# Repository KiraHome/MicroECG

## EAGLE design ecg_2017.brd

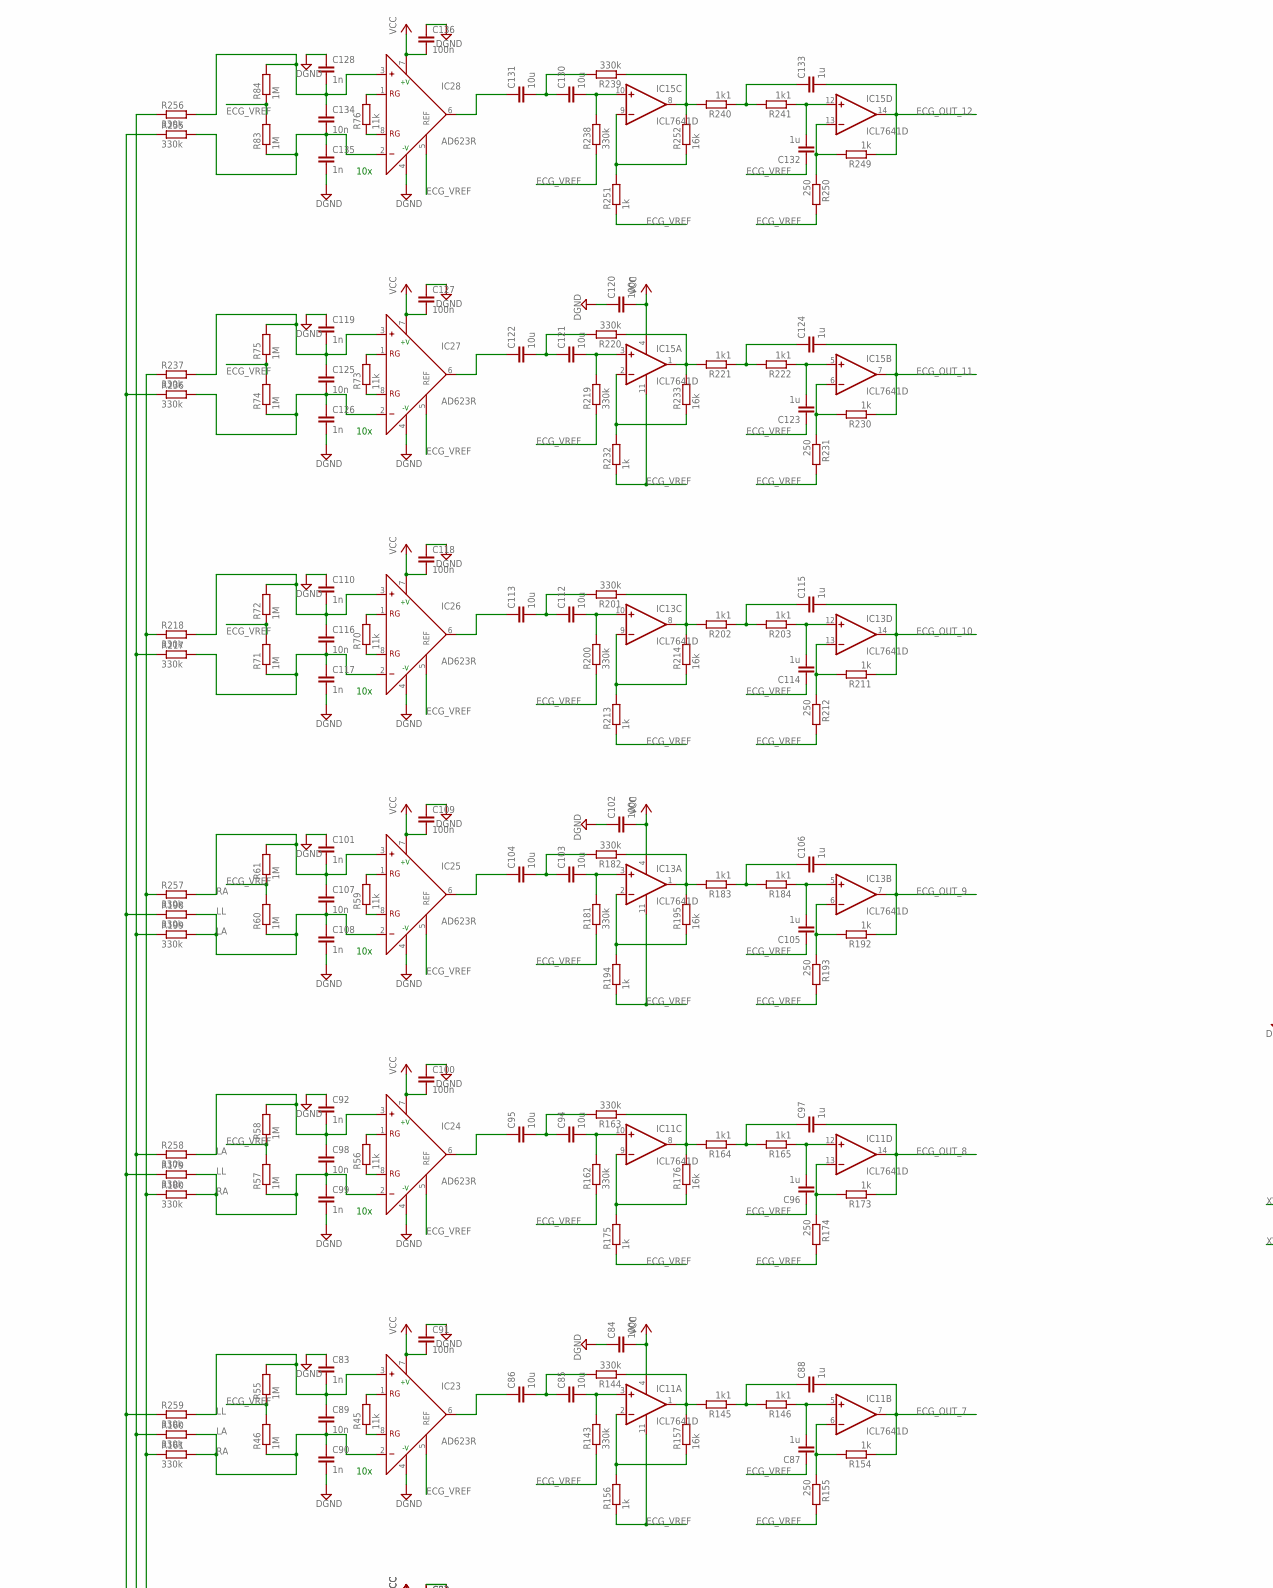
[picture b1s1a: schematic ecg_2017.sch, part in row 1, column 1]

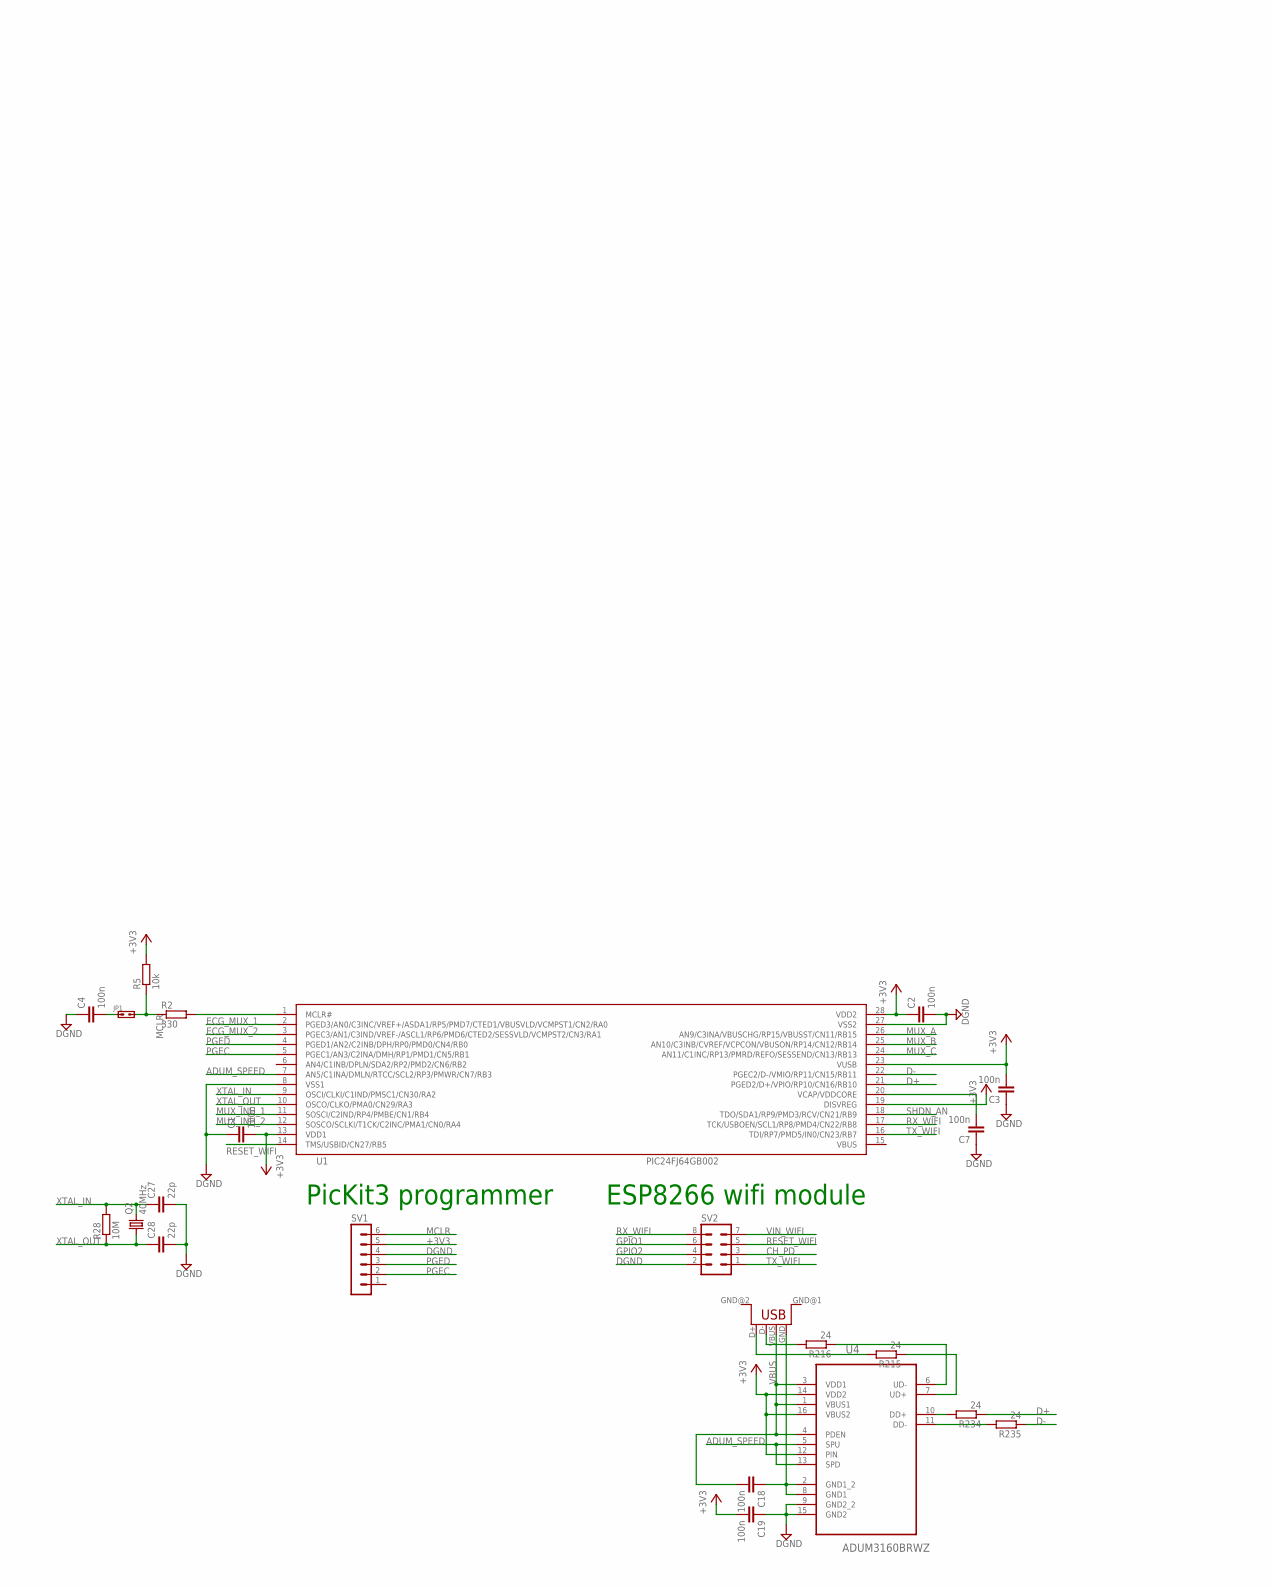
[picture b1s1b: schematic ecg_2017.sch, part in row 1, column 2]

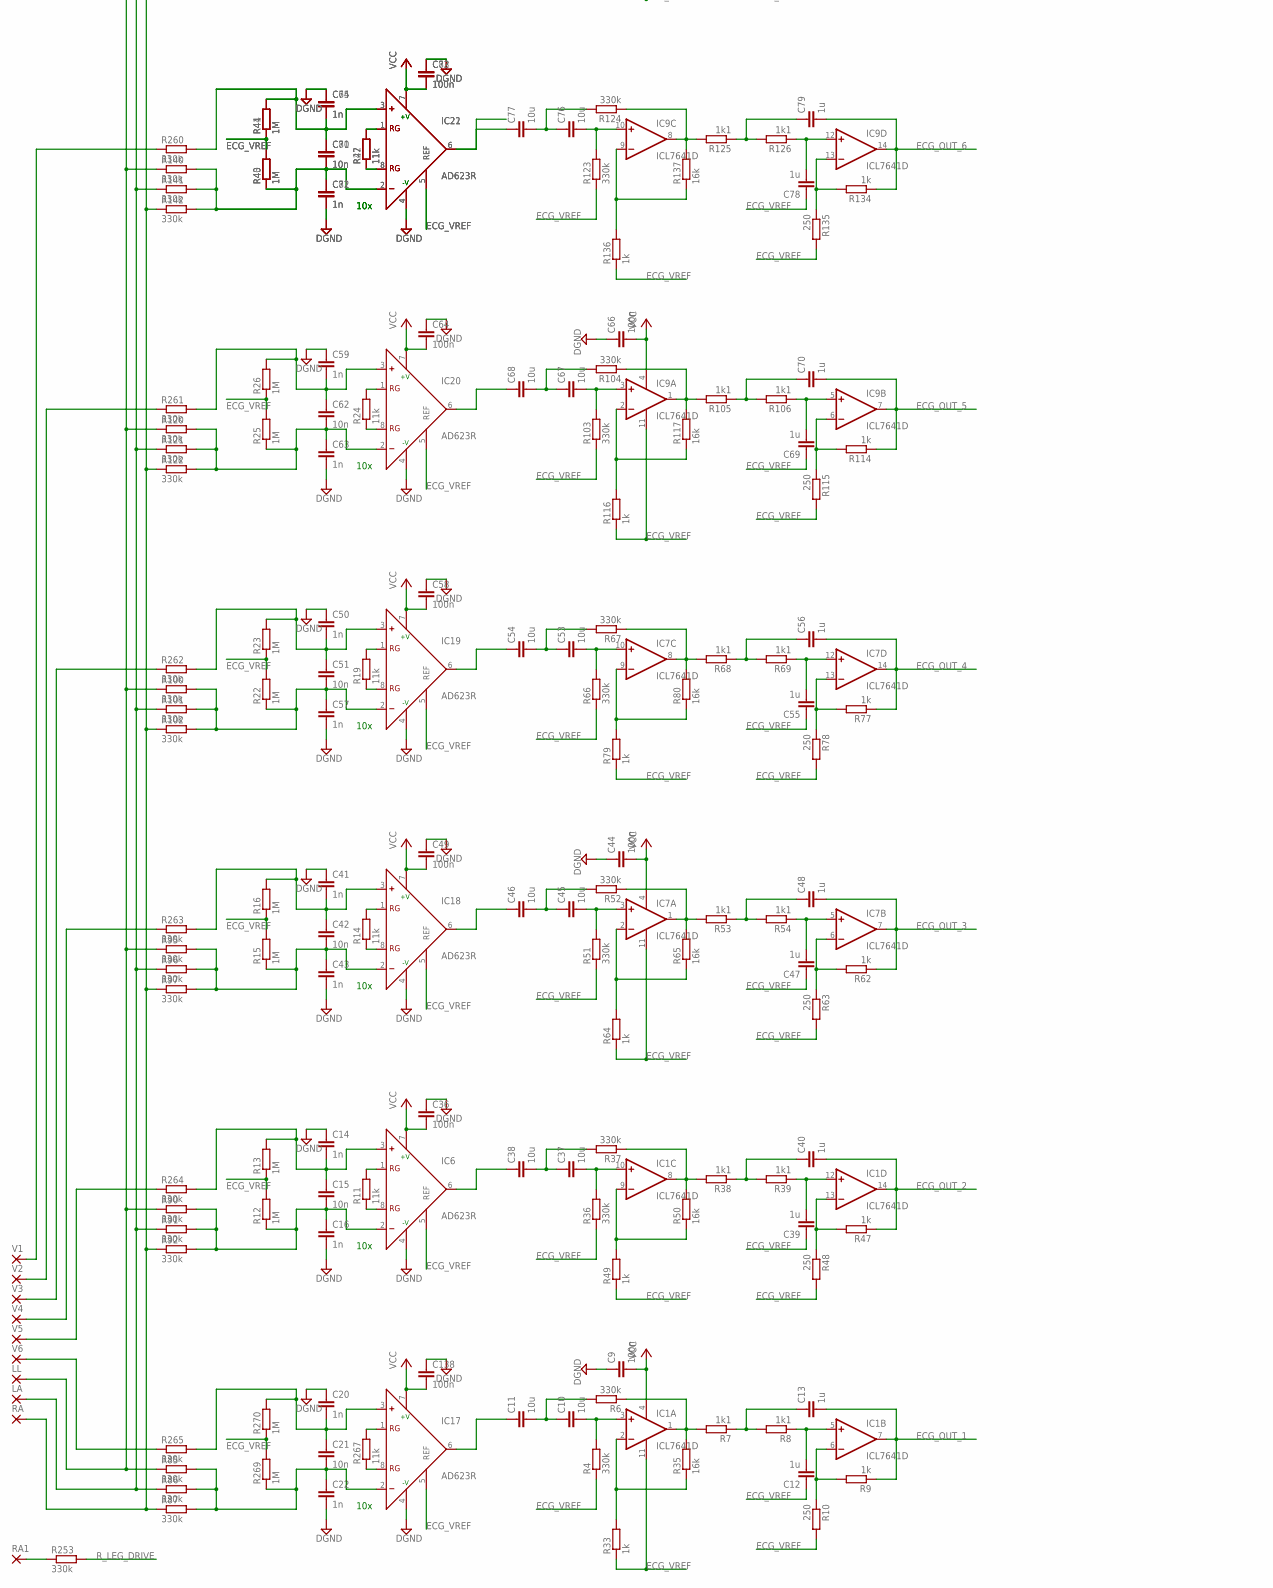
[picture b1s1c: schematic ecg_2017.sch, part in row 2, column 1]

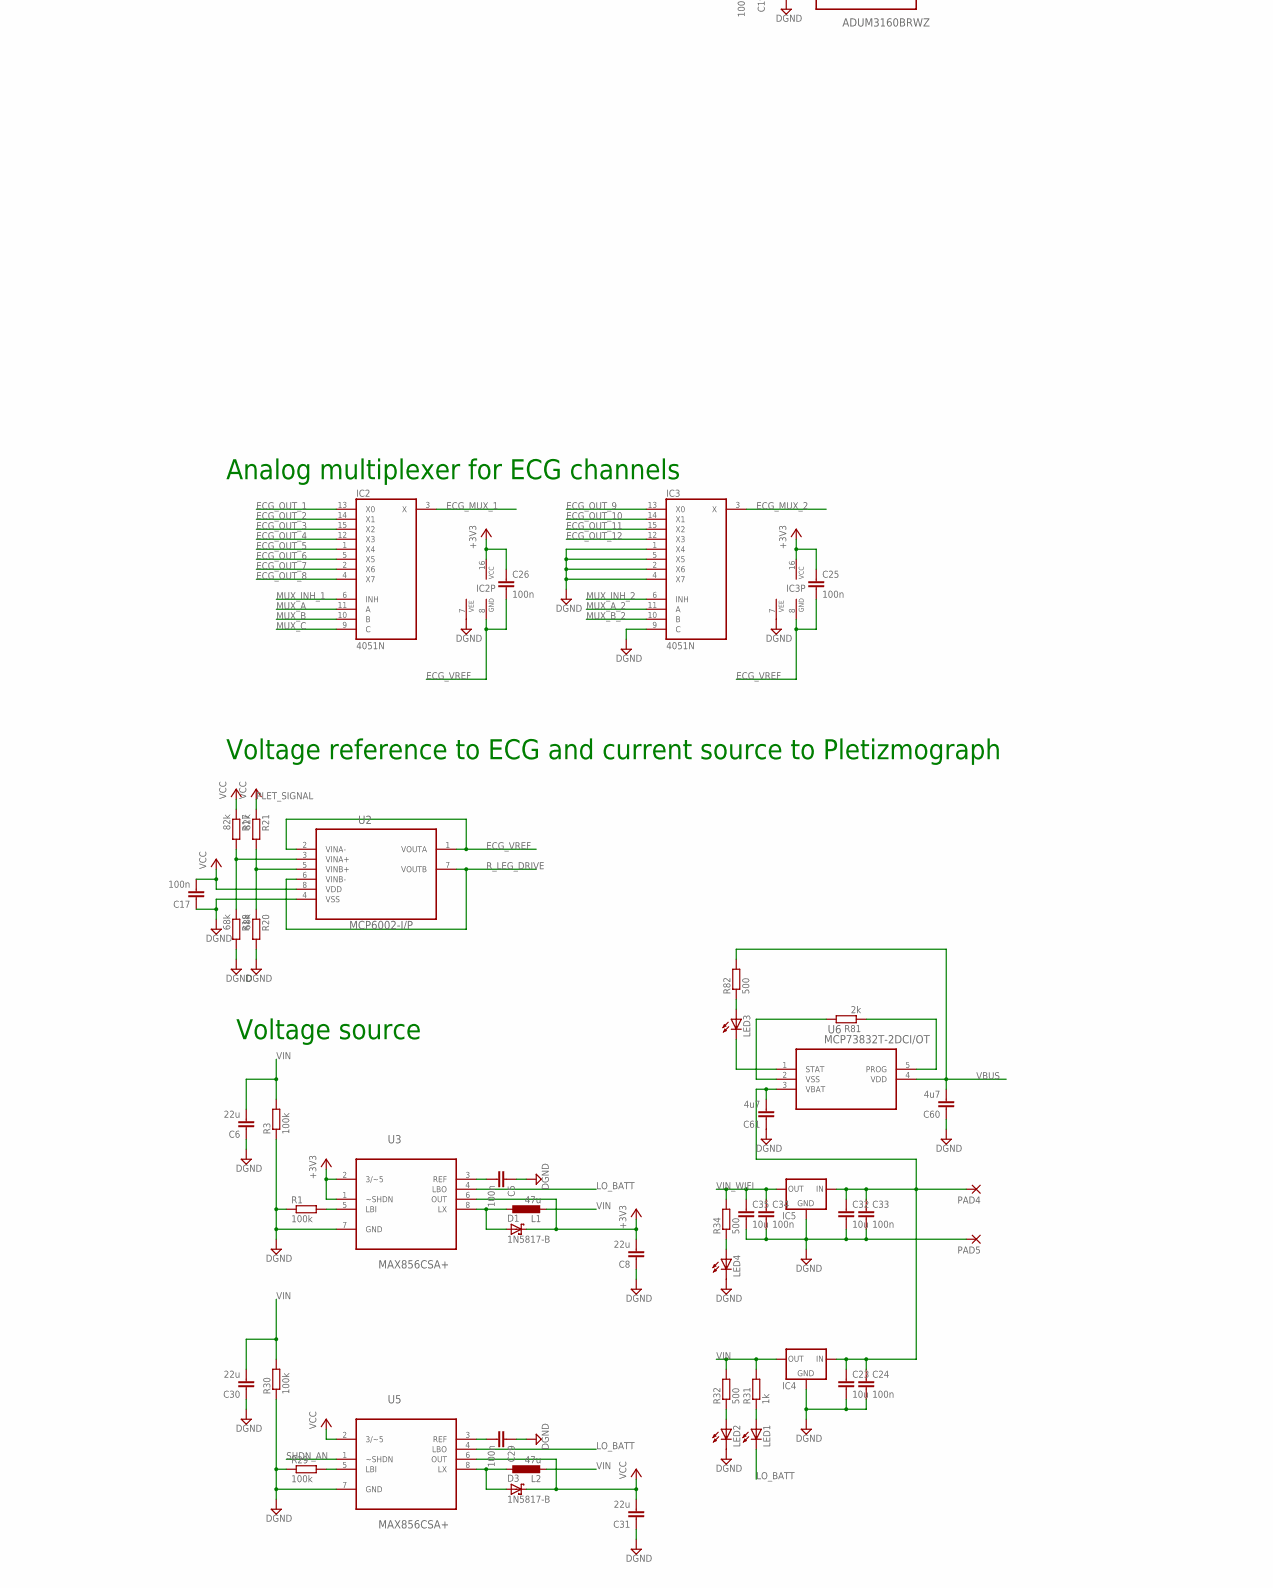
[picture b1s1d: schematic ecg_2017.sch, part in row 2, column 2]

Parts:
C1, C2, C3, C4, C5, C7, C9, C17, C18, C19, C24, C25, C26, C29, C33, C34, C36, C44, C49, C58, C64, C66, C73, C82, C84, C91, C100, C102, C109, C118, C120, C127, C136, C138: 100n; C0805
C6, C8, C30, C31: 22u; C0805
C10, C11, C23, C32, C35, C37, C38, C45, C46, C53, C54, C67, C68, C76, C77, C85, C86, C94, C95, C103, C104, C112, C113, C121, C122, C130, C131: 10u; C0805
C12, C13, C39, C40, C47, C48, C55, C56, C69, C70, C78, C79, C87, C88, C96, C97, C105, C106, C114, C115, C123, C124, C132, C133: 1u; C0805
C14, C16, C20, C22, C41, C43, C50, C57, C59, C63, C65, C72, C74, C81, C83, C90, C92, C99, C101, C108, C110, C117, C119, C126, C128, C135: 1n; C0805
C15, C21, C42, C51, C62, C71, C80, C89, C98, C107, C116, C125, C134: 10n; C0805
C27, C28: 22p; C0805
C60, C61: 4u7; C0805
CON2: USB; USB-FEMALE-A-PTH
D1, D3: 1N5817-B; DO41-7.6
IC1, IC7, IC9, IC11, IC13, IC15: ICL7641D; SO14
IC2, IC3: 4051N; DIL16
IC4, IC5: R-783.3-0.5; R-78XX
IC6, IC17, IC18, IC19, IC20, IC21, IC22, IC23, IC24, IC25, IC26, IC27, IC28: AD623R; SO8
JP1: JMP2; JP2
L1, L2: 47u; L1812
LA: 2,54/1,0
LED1, LED2, LED3, LED4: LEDSML0805; SML0805
LL: 2,54/1,0
PAD4, PAD5: 2,54/1,0
Q2: 40MHz; TC26V
R1, R3, R29, R30: 100k; R0805
R2: 330; R0805
R4, R6, R36, R37, R51, R52, R66, R67, R85, R86, R87, R90, R91, R92, R95, R96, R97, R100, R101, R102, R103, R104, R120, R121, R122, R123, R124, R140, R141, R142, R143, R144, R160, R161, R162, R163, R179, R180, R181, R182, R198, R199, R200, R201, R217, R218, R219, R220, R236, R237, R238, R239, R253, R255, R256, R257, R258, R259, R260, R261, R262, R263, R264, R265: 330k; R0805
R5: 10k; R0805
R7, R8, R38, R39, R53, R54, R68, R69, R105, R106, R125, R126, R145, R146, R164, R165, R183, R184, R202, R203, R221, R222, R240, R241: 1k1; R0805
R9, R31, R33, R47, R49, R62, R64, R77, R79, R114, R116, R134, R136, R154, R156, R173, R175, R192, R194, R211, R213, R230, R232, R249, R251: 1k; R0805
R10, R48, R63, R78, R115, R135, R155, R174, R193, R212, R231, R250: 250; R0805
R11, R14, R19, R24, R27, R42, R45, R56, R59, R70, R73, R76, R267: 11k; R0805
R12, R13, R15, R16, R22, R23, R25, R26, R40, R41, R43, R44, R46, R55, R57, R58, R60, R61, R71, R72, R74, R75, R83, R84, R269, R270: 1M; R0805
R17, R21: 82k; R0805
R18, R20: 68k; R0805
R28: 10M; M0805
R32, R34, R82: 500; R0805
R35, R50, R65, R80, R117, R137, R157, R176, R195, R214, R233, R252: 16k; R0805
R81: 2k; R0805
R215, R216, R234, R235: 24; R0805
RA, RA1: 2,54/1,0
SV1: MA06-1
SV2: MA04-2
U1: PIC24FJ64GB002; DIP28
U2: MCP6002-I/P; DIP254P762X533-8
U3, U5: MAX856CSA+; SOIC127P600X175-8N
U4: ADUM3160BRWZ; SOIC127P1032X265-16N
U6: MCP73832T-2DCI/OT; SOT95P300X145-5N
V1, V2, V3, V4, V5, V6: 2,54/1,0

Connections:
+3V3: C1.2, C2.1, C3.2, C8.2, C19.2, C25.1, C26.1, D1.C, IC2.16 (VCC), IC3.16 (VCC), R5.2, SV1.5, U1.13 (VDD1), U1.19 (DISVREG), U1.23 (VUSB), U1.28 (VDD2), U3.1 (~SHDN), U3.2 (3/~5), U3.6 (OUT), U4.12 (PIN), U4.14 (VDD2), U4.16 (VBUS2)
ADUM_SPEED: U1.7 (AN5/C1INA/DMLN/RTCC/SCL2/RP3/PMWR/CN7/R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), U4.5 (SPU), U4.13 (SPD)
CH_PD: SV2.3
D+: R234.1, U1.21 (PGED2/D+/VPIO/RP10/CN16/RB10)
D-: R235.1, U1.22 (PGEC2/D-/VMIO/RP11/CN15/RB11)
DGND: C1.1, C2.2, C3.1, C4.1, C5.1, C6.1, C7.1, C8.1, C9.1, C14.2, C16.1, C17.1, C19.1, C20.2, C22.1, C23.2, C24.2, C27.2, C28.2, C29.1, C30.1, C31.1, C32.2, C33.2, C34.2, C35.2, C36.2, C41.2, C43.1, C44.1, C49.2, C50.2, C57.1, C58.2, C59.2, C60.1, C61.1, C63.1, C64.2, C65.2, C66.1, C72.1, C73.2, C74.2, C81.1, C82.2, C83.2, C84.1, C90.1, C91.2, C92.2, C99.1, C100.2, C101.2, C102.1, C108.1, C109.2, C110.2, C117.1, C118.2, C119.2, C120.1, C126.1, C127.2, C128.2, C135.1, C136.2, C138.2, IC2.7 (VEE), IC3.1 (X4), IC3.2 (X6), IC3.4 (X7), IC3.5 (X5), IC3.7 (VEE), IC3.9 (C), IC4.GND, IC5.GND, IC6.4 (-V), IC17.4 (-V), IC18.4 (-V), IC19.4 (-V), IC20.4 (-V), IC21.4 (-V), IC22.4 (-V), IC23.4 (-V), IC24.4 (-V), IC25.4 (-V), IC26.4 (-V), IC27.4 (-V), IC28.4 (-V), LED2.C, LED4.C, PAD5.1, R1.1, R3.1, R18.2, R20.2, R29.1, R30.1, SV1.4, SV2.2, U1.8 (VSS1), U1.27 (VSS2), U2.4 (VSS), U3.7 (GND), U4.9 (GND2_2), U4.15 (GND2), U5.7 (GND)
ECG_MUX_1: IC2.3 (X), U1.2 (PGED3/AN0/C3INC/VREF+/ASDA1/RP5/PMD7/CT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)
ECG_MUX_2: IC3.3 (X), U1.3 (PGEC3/AN1/C3IND/VREF-/ASCL1/RP6/PMD6/CT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)
ECG_OUT_1: C13.2, IC1.7 (OUT), IC2.13 (X0), R9.1
ECG_OUT_2: C40.2, IC1.14 (OUT), IC2.14 (X1), R47.1
ECG_OUT_3: C48.2, IC2.15 (X2), IC7.7 (OUT), R62.1
ECG_OUT_4: C56.2, IC2.12 (X3), IC7.14 (OUT), R77.1
ECG_OUT_5: C70.2, IC2.1 (X4), IC9.7 (OUT), R114.1
ECG_OUT_6: C79.2, IC2.5 (X5), IC9.14 (OUT), R134.1
ECG_OUT_7: C88.2, IC2.2 (X6), IC11.7 (OUT), R154.1
ECG_OUT_8: C97.2, IC2.4 (X7), IC11.14 (OUT), R173.1
ECG_OUT_9: C106.2, IC3.13 (X0), IC13.7 (OUT), R192.1
ECG_OUT_10: C115.2, IC3.14 (X1), IC13.14 (OUT), R211.1
ECG_OUT_11: C124.2, IC3.15 (X2), IC15.7 (OUT), R230.1
ECG_OUT_12: C133.2, IC3.12 (X3), IC15.14 (OUT), R249.1
ECG_VREF: C12.1, C25.2, C26.2, C39.1, C47.1, C55.1, C69.1, C78.1, C87.1, C96.1, C105.1, C114.1, C123.1, C132.1, IC1.11 (V-), IC2.8 (GND), IC3.8 (GND), IC6.5 (REF), IC7.11 (V-), IC9.11 (V-), IC11.11 (V-), IC13.11 (V-), IC15.11 (V-), IC17.5 (REF), IC18.5 (REF), IC19.5 (REF), IC20.5 (REF), IC21.5 (REF), IC22.5 (REF), IC23.5 (REF), IC24.5 (REF), IC25.5 (REF), IC26.5 (REF), IC27.5 (REF), IC28.5 (REF), R4.1, R10.2, R12.2, R13.1, R15.2, R16.1, R22.2, R23.1, R25.2, R26.1, R33.1, R36.1, R40.2, R41.1, R43.2, R44.1, R46.2, R48.2, R49.1, R51.1, R55.1, R57.2, R58.1, R60.2, R61.1, R63.2, R64.1, R66.1, R71.2, R72.1, R74.2, R75.1, R78.2, R79.1, R83.2, R84.1, R103.1, R115.2, R116.1, R123.1, R135.2, R136.1, R143.1, R155.2, R156.1, R162.1, R174.2, R175.1, R181.1, R193.2, R194.1, R200.1, R212.2, R213.1, R219.1, R231.2, R232.1, R238.1, R250.2, R251.1, R269.2, R270.1, U2.1 (VOUTA), U2.2 (VINA-)
GPIO1: SV2.6
GPIO2: SV2.4
LA: LA.1, R86.1, R91.1, R96.1, R101.1, R121.1, R141.1, R160.1, R199.1, R217.1, R256.1, R258.1
LL: LL.1, R85.1, R90.1, R95.1, R100.1, R120.1, R140.1, R179.1, R198.1, R236.1, R255.1, R259.1
LO_BATT: LED1.C, U3.4 (LBO), U5.4 (LBO)
MCLR: JP1.2, R2.1, R5.1, SV1.6
MUX_A: IC2.11 (A), U1.26 (AN9/C3INA/VBUSCHG/RP15/VBUSST/CN11/RB15)
MUX_A_2: IC3.11 (A)
MUX_B: IC2.10 (B), U1.25 (AN10/C3INB/CVREF/VCPCON/VBUSON/RP14/CN1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)
MUX_B_2: IC3.10 (B)
MUX_C: IC2.9 (C), U1.24 (AN11/C1INC/RP13/PMRD/REFO/SESSEND/CN13/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)
MUX_INH_1: IC2.6 (INH), U1.11 (SOSCI/C2IND/RP4/PMBE/CN1/RB4)
MUX_INH_2: IC3.6 (INH), U1.12 (SOSCO/SCLKI/T1CK/C2INC/PMA1/CN0/RA4)
unnamed: C5.2, U3.3 (REF)
unnamed: R1.2, U3.5 (LBI)
unnamed: C10.2, IC1.3 (+IN), R4.2
unnamed: D1.A, L1.1, U3.8 (LX)
unnamed: C10.1, C11.2, R6.2
unnamed: IC1.2 (-IN), R33.2, R35.1
unnamed: C13.1, R7.1, R8.2
unnamed: C12.2, IC1.5 (+IN), R8.1
unnamed: IC6.8 (RG), R11.1
unnamed: C4.2, JP1.1
unnamed: R2.2, U1.1 (MCLR#)
unnamed: IC6.1 (RG), R11.2
unnamed: C134.1, C135.2, IC28.2 (-), R83.1, R255.2
unnamed: C14.1, C15.2, IC6.3 (+), R13.2, R264.2
unnamed: C38.1, IC6.6 (OUT)
unnamed: IC18.8 (RG), R14.1
unnamed: IC18.1 (RG), R14.2
unnamed: R17.2, R18.1, U2.3 (VINA+)
unnamed: IC17.8 (RG), R267.1
unnamed: IC1.6 (-IN), R9.2, R10.1
unnamed: C41.1, C42.2, IC18.3 (+), R16.2, R263.2
unnamed: C29.2, U5.3 (REF)
unnamed: C46.1, IC18.6 (OUT)
unnamed: IC19.8 (RG), R19.1
unnamed: C23.1, C24.1, C32.1, C33.1, C61.2, IC4.IN, IC5.IN, PAD4.1, U6.3 (VBAT)
unnamed: R81.1, U6.5 (PROG)
unnamed: R81.2, U6.2 (VSS)
unnamed: LED3.A, R82.1
unnamed: LED3.C, U6.1 (STAT)
unnamed: IC19.1 (RG), R19.2
unnamed: C50.1, C51.2, IC19.3 (+), R23.2, R262.2
unnamed: C54.1, IC19.6 (OUT)
unnamed: IC28.8 (RG), R76.1
unnamed: IC20.8 (RG), R24.1
unnamed: IC20.1 (RG), R24.2
unnamed: C59.1, C62.2, IC20.3 (+), R26.2, R261.2
unnamed: C68.1, IC20.6 (OUT)
unnamed: R29.2, U5.5 (LBI)
unnamed: C7.2, U1.20 (VCAP/VDDCORE)
unnamed: D3.A, L2.1, U5.8 (LX)
unnamed: LED1.A, R31.1
unnamed: LED2.A, R32.1
unnamed: C37.2, IC1.10 (+IN), R36.2
unnamed: IC1.1 (OUT), R6.1, R7.2, R35.2
unnamed: LED4.A, R34.1
unnamed: C37.1, C38.2, R37.2
unnamed: C40.1, R38.1, R39.2
unnamed: C39.2, IC1.12 (+IN), R39.1
unnamed: IC28.1 (RG), R76.2
unnamed: IC21.8 (RG), R27.1
unnamed: IC21.1 (RG), R27.2
unnamed: C65.1, C71.2, IC21.3 (+), R41.2, R260.2
unnamed: C77.1, IC21.6 (OUT)
unnamed: IC17.1 (RG), R267.2
unnamed: C80.1, C81.2, IC22.2 (-), R43.1
unnamed: C89.1, C90.2, IC23.2 (-), R46.1, R160.2, R161.2
unnamed: IC1.13 (-IN), R47.2, R48.1
unnamed: IC1.8 (OUT), R37.1, R38.2, R50.2
unnamed: IC1.9 (-IN), R49.2, R50.1
unnamed: C45.2, IC7.3 (+IN), R51.2
unnamed: C45.1, C46.2, R52.2
unnamed: C48.1, R53.1, R54.2
unnamed: C47.2, IC7.5 (+IN), R54.1
unnamed: C98.1, C99.2, IC24.2 (-), R57.1, R179.2, R180.2
unnamed: C107.1, C108.2, IC25.2 (-), R60.1, R198.2, R199.2
unnamed: C116.1, C117.2, IC26.2 (-), R71.1, R217.2
unnamed: C125.1, C126.2, IC27.2 (-), R74.1, R236.2
unnamed: IC22.8 (RG), R42.1
unnamed: IC22.1 (RG), R42.2
unnamed: C74.1, C80.2, IC22.3 (+), R44.2
unnamed: IC7.6 (-IN), R62.2, R63.1
unnamed: IC7.1 (OUT), R52.1, R53.2, R65.2
unnamed: IC7.2 (-IN), R64.2, R65.1
unnamed: C53.2, IC7.10 (+IN), R66.2
unnamed: C53.1, C54.2, R67.2
unnamed: C56.1, R68.1, R69.2
unnamed: C55.2, IC7.12 (+IN), R69.1
unnamed: IC23.8 (RG), R45.1
unnamed: IC23.1 (RG), R45.2
unnamed: C83.1, C89.2, IC23.3 (+), R55.2, R259.2
unnamed: C86.1, IC23.6 (OUT)
unnamed: C20.1, C21.2, IC17.3 (+), R265.2, R270.2
unnamed: IC24.8 (RG), R56.1
unnamed: IC24.1 (RG), R56.2
unnamed: IC7.13 (-IN), R77.2, R78.1
unnamed: IC7.8 (OUT), R67.1, R68.2, R80.2
unnamed: IC7.9 (-IN), R79.2, R80.1
unnamed: C21.1, C22.2, IC17.2 (-), R85.2, R86.2, R87.2, R269.1
unnamed: C128.1, C134.2, IC28.3 (+), R84.2, R256.2
unnamed: C112.2, IC13.10 (+IN), R200.2
unnamed: C112.1, C113.2, R201.2
unnamed: R265.1, V6.1
unnamed: C92.1, C98.2, IC24.3 (+), R58.2, R258.2
unnamed: C15.1, C16.2, IC6.2 (-), R12.1, R90.2, R91.2, R92.2
unnamed: R264.1, V5.1
unnamed: C18.1, CON2.GND, U4.2 (GND1_2), U4.8 (GND1)
unnamed: C95.1, IC24.6 (OUT)
unnamed: C76.2, IC9.10 (+IN), R123.2
unnamed: R263.1, V4.1
unnamed: R216.1, U4.6 (UD-)
unnamed: R215.1, U4.7 (UD+)
unnamed: R262.1, V3.1
unnamed: C42.1, C43.2, IC18.2 (-), R15.1, R95.2, R96.2, R97.2
unnamed: C51.1, C57.2, IC19.2 (-), R22.1, R100.2, R101.2, R102.2
unnamed: C76.1, C77.2, R124.2
unnamed: C67.2, IC9.3 (+IN), R103.2
unnamed: C67.1, C68.2, R104.2
unnamed: C70.1, R105.1, R106.2
unnamed: C69.2, IC9.5 (+IN), R106.1
unnamed: IC25.8 (RG), R59.1
unnamed: IC25.1 (RG), R59.2
unnamed: C101.1, C107.2, IC25.3 (+), R61.2, R257.2
unnamed: C104.1, IC25.6 (OUT)
unnamed: C11.1, IC17.6 (OUT)
unnamed: IC26.8 (RG), R70.1
unnamed: IC26.1 (RG), R70.2
unnamed: IC9.6 (-IN), R114.2, R115.1
unnamed: IC9.1 (OUT), R104.1, R105.2, R117.2
unnamed: IC9.2 (-IN), R116.2, R117.1
unnamed: CON2.D-, R216.2
unnamed: R234.2, U4.10 (DD+)
unnamed: C110.1, C116.2, IC26.3 (+), R72.2, R218.2
unnamed: C62.1, C63.2, IC20.2 (-), R25.1, R120.2, R121.2, R122.2
unnamed: C79.1, R125.1, R126.2
unnamed: C78.2, IC9.12 (+IN), R126.1
unnamed: C113.1, IC26.6 (OUT)
unnamed: IC27.8 (RG), R73.1
unnamed: IC27.1 (RG), R73.2
unnamed: C119.1, C125.2, IC27.3 (+), R75.2, R237.2
unnamed: C122.1, IC27.6 (OUT)
unnamed: C131.1, IC28.6 (OUT)
unnamed: IC9.13 (-IN), R134.2, R135.1
unnamed: IC9.8 (OUT), R124.1, R125.2, R137.2
unnamed: IC9.9 (-IN), R136.2, R137.1
unnamed: CON2.D+, R215.2
unnamed: R235.2, U4.11 (DD-)
unnamed: R260.1, V1.1
unnamed: C71.1, C72.2, IC21.2 (-), R40.1, R140.2, R141.2, R142.2
unnamed: R261.1, V2.1
unnamed: C94.2, IC11.10 (+IN), R162.2
unnamed: C85.2, IC11.3 (+IN), R143.2
unnamed: C85.1, C86.2, R144.2
unnamed: C88.1, R145.1, R146.2
unnamed: C87.2, IC11.5 (+IN), R146.1
unnamed: IC11.6 (-IN), R154.2, R155.1
unnamed: IC11.1 (OUT), R144.1, R145.2, R157.2
unnamed: IC11.2 (-IN), R156.2, R157.1
unnamed: R253.1, RA1.1
unnamed: C94.1, C95.2, R163.2
unnamed: C115.1, R202.1, R203.2
unnamed: C97.1, R164.1, R165.2
unnamed: C96.2, IC11.12 (+IN), R165.1
unnamed: IC11.13 (-IN), R173.2, R174.1
unnamed: IC11.8 (OUT), R163.1, R164.2, R176.2
unnamed: IC11.9 (-IN), R175.2, R176.1
unnamed: C103.2, IC13.3 (+IN), R181.2
unnamed: C103.1, C104.2, R182.2
unnamed: C106.1, R183.1, R184.2
unnamed: C105.2, IC13.5 (+IN), R184.1
unnamed: IC13.6 (-IN), R192.2, R193.1
unnamed: IC13.1 (OUT), R182.1, R183.2, R195.2
unnamed: IC13.2 (-IN), R194.2, R195.1
unnamed: C114.2, IC13.12 (+IN), R203.1
unnamed: IC13.13 (-IN), R211.2, R212.1
unnamed: IC13.8 (OUT), R201.1, R202.2, R214.2
unnamed: IC13.9 (-IN), R213.2, R214.1
unnamed: C121.2, IC15.3 (+IN), R219.2
unnamed: C121.1, C122.2, R220.2
unnamed: C124.1, R221.1, R222.2
unnamed: C123.2, IC15.5 (+IN), R222.1
unnamed: IC15.6 (-IN), R230.2, R231.1
unnamed: IC15.1 (OUT), R220.1, R221.2, R233.2
unnamed: IC15.2 (-IN), R232.2, R233.1
unnamed: C130.2, IC15.10 (+IN), R238.2
unnamed: C130.1, C131.2, R239.2
unnamed: C133.1, R240.1, R241.2
unnamed: C132.2, IC15.12 (+IN), R241.1
unnamed: IC15.13 (-IN), R249.2, R250.1
unnamed: IC15.8 (OUT), R239.1, R240.2, R252.2
unnamed: IC15.9 (-IN), R251.2, R252.1
PGEC: SV1.2, U1.5 (PGEC1/AN3/C2INA/DMH/RP1/PMD1/CN5/RB1)
PGED: SV1.3, U1.4 (PGED1/AN2/C2INB/DPH/RP0/PMD0/CN4/RB0)
PLET_SIGNAL: R20.1, R21.2, U2.5 (VINB+)
RA: R87.1, R92.1, R97.1, R102.1, R122.1, R142.1, R161.1, R180.1, R218.1, R237.1, R257.1, RA.1
RESET_WIFI: SV2.5, U1.14 (TMS/USBID/CN27/RB5)
RX_WIFI: SV2.8, U1.17 (TCK/USBOEN/SCL1/RP8/PMD4/CN22/RB8)
R_LEG_DRIVE: R253.2, U2.6 (VINB-), U2.7 (VOUTB)
SHDN_AN: U1.18 (TDO/SDA1/RP9/PMD3/RCV/CN21/RB9), U5.1 (~SHDN)
TX_WIFI: SV2.1, U1.16 (TDI/RP7/PMD5/IN0/CN23/RB7)
VBUS: C18.2, C60.2, CON2.VBUS, R82.2, U1.15 (VBUS), U4.1 (VBUS1), U4.3 (VDD1), U4.4 (PDEN), U6.4 (VDD)
VCC: C9.2, C17.2, C31.2, C36.1, C44.2, C49.1, C58.1, C64.1, C66.2, C73.1, C82.1, C84.2, C91.1, C100.1, C102.2, C109.1, C118.1, C120.2, C127.1, C136.1, C138.1, D3.C, IC1.4 (V+), IC6.7 (+V), IC7.4 (V+), IC9.4 (V+), IC11.4 (V+), IC13.4 (V+), IC15.4 (V+), IC17.7 (+V), IC18.7 (+V), IC19.7 (+V), IC20.7 (+V), IC21.7 (+V), IC22.7 (+V), IC23.7 (+V), IC24.7 (+V), IC25.7 (+V), IC26.7 (+V), IC27.7 (+V), IC28.7 (+V), R17.1, R21.1, U2.8 (VDD), U5.2 (3/~5), U5.6 (OUT)
VIN: C6.2, C30.2, IC4.OUT, L1.2, L2.2, R3.2, R30.2, R31.2, R32.2
VIN_WIFI: C34.1, C35.1, IC5.OUT, R34.2, SV2.7
XTAL_IN: C27.1, Q2.2, R28.2, U1.9 (OSCI/CLKI/C1IND/PMSC1/CN30/RA2)
XTAL_OUT: C28.1, Q2.1, R28.1, U1.10 (OSCO/CLKO/PMA0/CN29/RA3)

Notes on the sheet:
PicKit3 programmer
ESP8266 wifi module
Voltage source
Voltage reference to ECG and current source to Pletizmograph
Analog multiplexer for ECG channels
10x

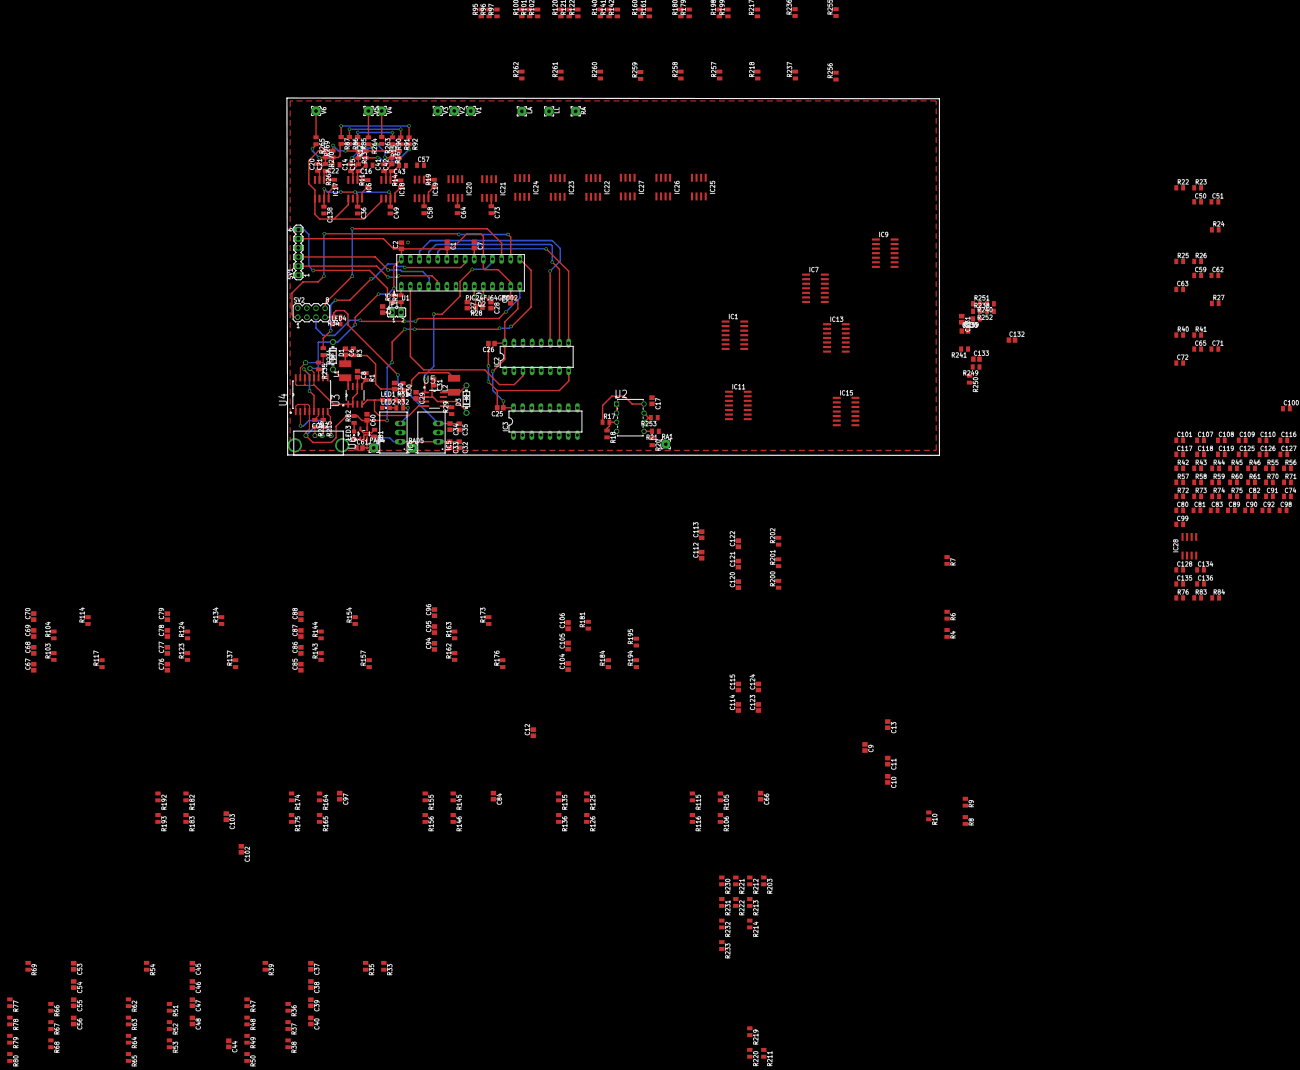
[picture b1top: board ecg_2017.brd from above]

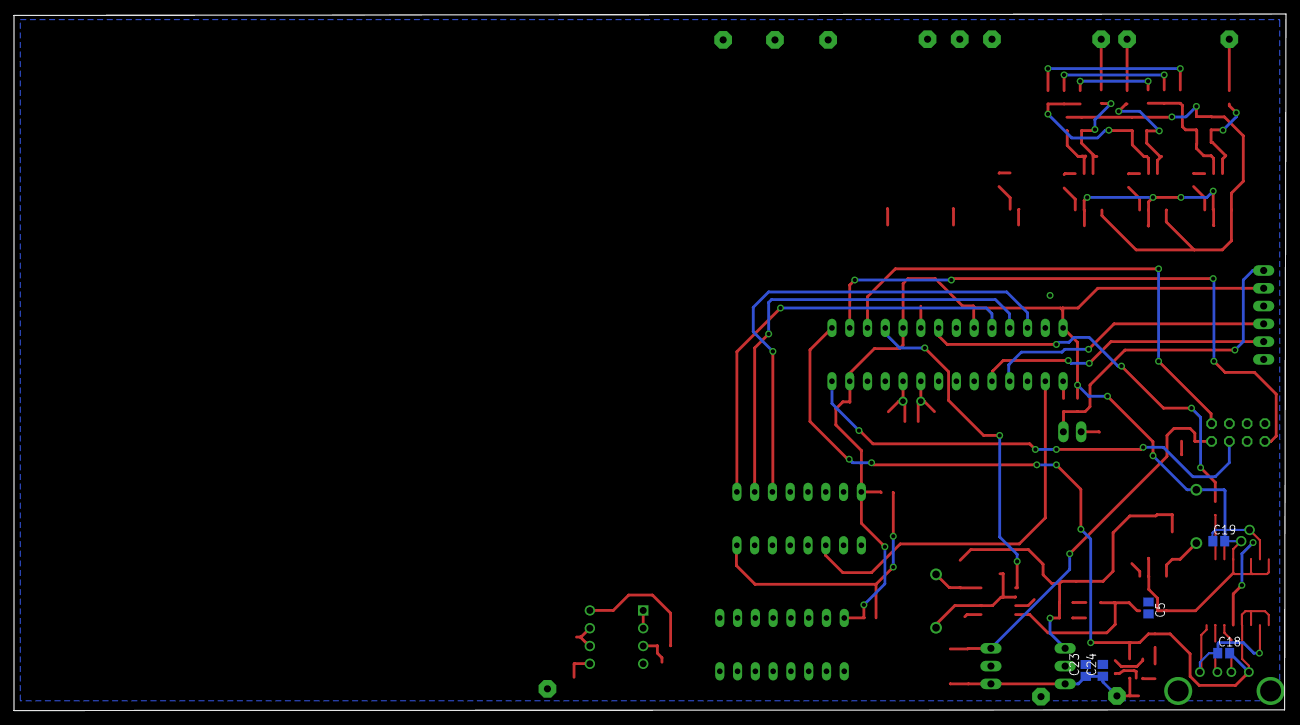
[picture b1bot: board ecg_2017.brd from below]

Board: 2 copper layers, 181.7 x 99.5 mm, 381 parts (5 on the bottom side), 224 nets.
